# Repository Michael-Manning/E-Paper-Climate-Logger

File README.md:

# Weathergotchi - an E-Paper Climate Logger

## About

This project is an open-source, battery-powered temperature and humidity data logger with an always-on e-paper display. It records ambient conditions over time, stores readings in non-volatile memory, and displays current data along with a history graph. The device is designed for low power consumption, over 2 weeks of operation on a small Li‑Po battery.

Key features:

- ESP32-S3 with deep sleep & RTC timer to wake up
- Temperature and humidity sensor with external EEPROM for logging
- Accurate battery monitoring and charging management
- Power button controller to turn on/off
- 1.54‑inch e‑paper display
- Custom PCB & 3D‑printed case
- Over 2 weeks of battery life on a single charge

The entire project is open source, including hardware schematics, PCB layout, firmware, and enclosure CAD files. A detailed build video is available on YouTube: [E-Paper Climate Logger](https://www.youtube.com/watch?v=I44iGj7gLGA).

### Youtube video

## Repository Structure

```
E-Paper-Climate-Logger/
├── CAD/                 # 3D case design (OpenSCAD source and STL exports)
├── PCB/                 # KiCad hardware design, schematics, datasheets, references
├── firmware/            # PlatformIO firmware (ESP32-S3, Arduino framework)
├── LICENSE              # License file
└── README.md            # This file
```

### CAD

Contains the parametric OpenSCAD models for the front and back case halves, assembly files, and exported STLs for 3D printing. The design is fully parametric – dimensions can be adjusted by editing `constants.scad`.

### PCB

All hardware design files for the custom mainboard (`templog_mainboard`). This directory includes:

- KiCad project files (`.kicad_sch`, `.kicad_pcb`, `.kicad_pro`)
- Schematic sheets for power management and display driver
- Component footprints and 3D models
- Datasheets for all major ICs (charger, fuel gauge, RTC, sensors, etc.)
- Reference schematics from SparkFun and Waveshare

To view or modify the PCB design, install KiCad 9 or later and open `templog_mainboard.kicad_pro`.

### Firmware

PlatformIO project for the ESP32‑S3 using the Arduino framework. It handles sensor reading, timekeeping, data logging to EEPROM, e‑paper display updates, button handling, and power management (deep sleep, wake sources). See `firmware/README.md` for detailed build and flashing instructions.

## Getting Started

### Hardware Prerequisites

- Assembled E-Paper Climate Logger PCB (or a hand‑soldered prototype – note that many components are small and may require reflow soldering)
- 1.54‑inch e‑paper display (compatible with Waveshare pinout)
- 3D‑printed case (files in `CAD/export/`)
- Li‑Po battery (e.g., 400 mAh, single cell)
- USB‑C cable for charging and programming

### Building the Firmware

1. Install [PlatformIO Core](https://platformio.org/install/cli) (or use the PlatformIO extension in VS Code).
2. Navigate to the `firmware` directory.
3. Connect the device via USB‑C.
4. Run:

   ```
   pio run --target upload
   ```

5. Monitor serial output (optional):

   ```
   pio device monitor
   ```

For detailed firmware documentation, including folder structure, driver details, and low‑power operation, refer to [`firmware/README.md`](firmware/README.md).

### Enclosure Assembly

Print the STL files from `CAD/V2/export/` using a high‑resolution FDM printer (0.08 mm layer height recommended). The case uses M2 heat set inserts and M2 screws. Insert the PCB and battery, then screw the front and back halves together. See note.txt in CAD\V2 for more details.

## Hardware Overview

All I2C peripherals (SHT45, DS3231, 24LC512, BQ27441) share the same bus. The e‑paper display is driven via SPI, and the LTC2954 soft power button controls system power-off via the BQ24075.

For complete schematics and PCB layout, open the KiCad project in `PCB/templog_mainboard/`.

## Power Management and Low‑Power Operation

The device is designed to run for over 2 weeks on a small battery:

- In deep sleep, the ESP32‑S3 draws less than 20 µA. The DS3231 and BQ27441 remain active with negligible current.
- The DS3231 alarm wakes the ESP32 at a configurable interval (default: 1 minute). The ESP32 wakes, logs a reading (about 400 ms at 50 mA), updates the display, and returns to sleep.
- The LTC2954 provides a true on/off capability.

## Issues
- **Battery accuracy issues**: In my testing, the reported battery state of charge is not accurate. I believe this is due to a misconfiguration BQ27441.
- **Low battery issues**: In my testing, when connecting a battery to the device, it will sometimes not turn on until the battery has been connected/disconnected multiple times. 

## Notes on building your own device

I don't have a detailed build guide on how to build your own device at this time, but if you do decide to make one, these are some details you should know.

- First firmware upload requires putting the ESP32-S3 in boot mode. There are three pads near the battery input that expose, BOOT, Enable, and ground. Attaching leads to these pins will allow you to put the ESP32 in boot mode.
- The back of the PCB must be completely flat in order to fit in the case with the screen. After soldering through-hole components. like the buttons, you may need a dremel to flatten the leads/solder on the back of the PCB.

## Troubleshooting

- **Device does not power/stay on:** Ensure the battery is charged to at least 3.7V and try disconnecting/reconnecting the battery. Sometimes the battery must be reconnected multiple times before booting for the first time.
- **Battery percentage inaccurate:** The BQ27441 requires a one-time capacity configuration; refer to the datasheet and adjust `BQ27441.cpp`. The fuel gauge also needs to "learn" the battery before it reports an accurate  state of charge. Fully charge the battery, then wait for it to completely deplete. This will help the fuel gauge report a more accurate charge level.
- **Cannot upload program to the device:** Before uploading for the first time, the device must be manually put in boot mode. See the above note in building your own device.

## Limitations
- **Temperature accuracy during handling**: The ESP32 generates heat when active, which can affect the SHT45 reading. The firmware reads the sensor immediately upon wake to minimize this error. Prolonged menu browsing or holding the device will skew the ambient reading for several minutes.
- **Display low‑temperature limit**: The e‑paper module is rated for operation above 0°C. Below freezing, the screen may not update reliably. Data logging continues in the background, and display functionality resumes when the temperature rises.
- **No wireless connectivity**: While this device has the physical capability for bluetooth and WIFI, The current version of the firmware does not support it or allow you to use the radio to export data. Data can be viewed only on the device screen.

## Contributing

Issues, pull requests, and suggestions are welcome. Please follow the existing code style and document any changes to the hardware or firmware.

## License

Refer to the `LICENSE` file in the root directory for licensing terms (open source, permissive).

## Acknowledgements

- SparkFun for the Battery Babysitter reference design
- Waveshare for e‑paper display modules and driver schematics
- The PlatformIO and GxEPD2 communities

For questions or discussions, open an issue on GitHub or visit the YouTube video comments.

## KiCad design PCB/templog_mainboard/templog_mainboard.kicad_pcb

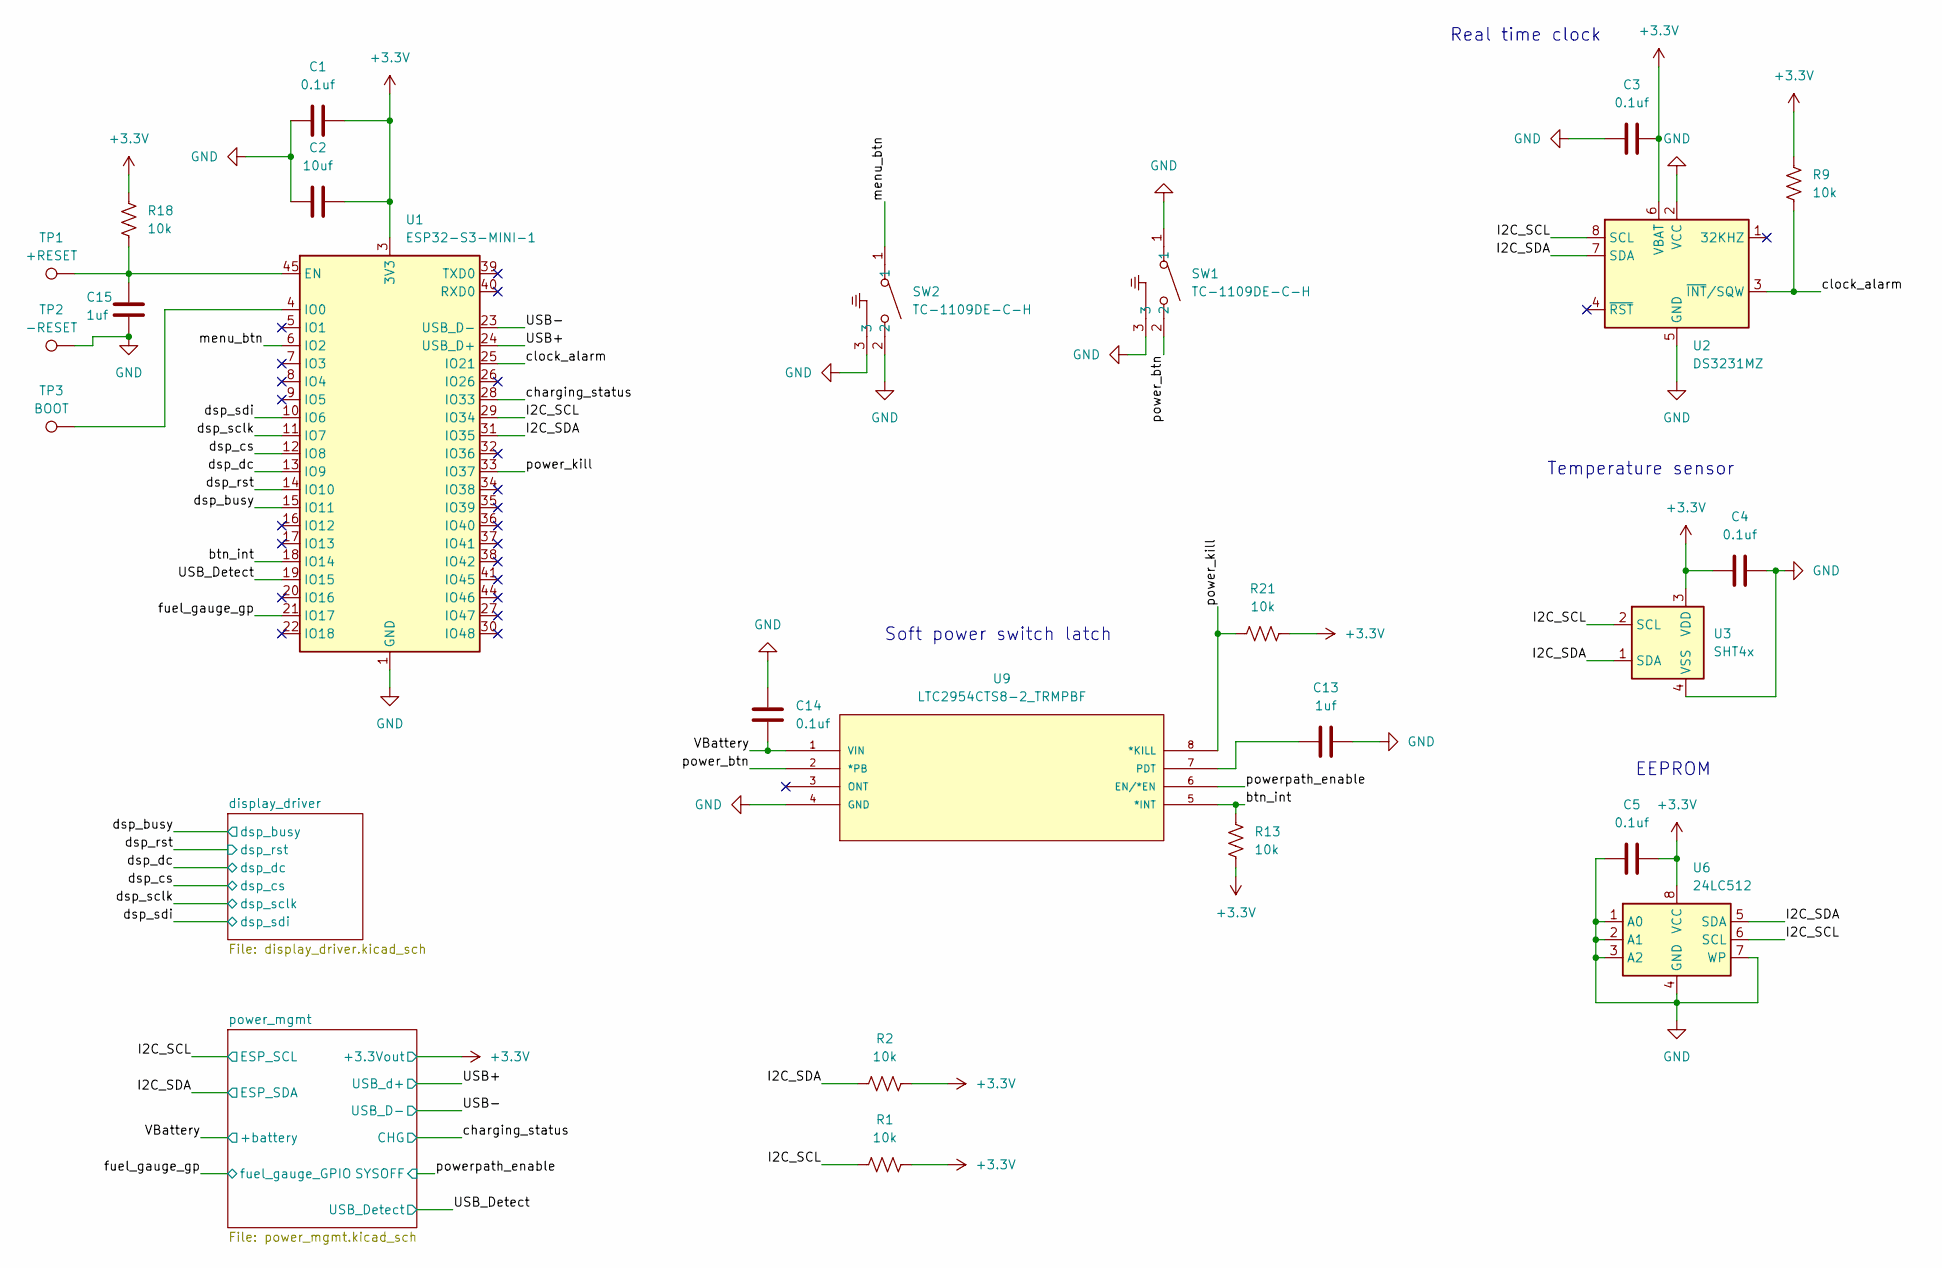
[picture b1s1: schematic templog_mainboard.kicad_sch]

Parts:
C1, C3, C4, C5, C14: 0.1uf; C_0402_1005Metric
C2: 10uf; C_0805_2012Metric
C13: 1uf; C_0603_1608Metric
C15: 1uf; C_0402_1005Metric
R1, R2, R9, R13, R18, R21: 10k; R_0402_1005Metric
SW1, SW2: TC-1109DE-C-H; SW-TH_TC-1109DE-C-H; LCSC Part C400335
TP1: +RESET; TestPoint_Pad_1.0x1.0mm
TP2: -RESET; TestPoint_Pad_1.0x1.0mm
TP3: BOOT; TestPoint_Pad_1.0x1.0mm
U1: ESP32-S3-MINI-1; ESP32-S2-MINI-1; LCSC Part # C2913206
U2: DS3231MZ; SOIC-8_3.9x4.9mm_P1.27mm; LCSC Part # C107410
U3: SHT4x; Sensirion_DFN-4_1.5x1.5mm_P0.8mm_SHT4x_NoCentralPad; LCSC Part # C5360602
U6: 24LC512; SOIC-8_3.9x4.9mm_P1.27mm; LCSC Part # C52088
U9: LTC2954CTS8-2_TRMPBF; TSOT-23_TS8; MANUFACTURER_PART_NUMBER ltc2954cts81; LCSC Part # C580656

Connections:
+3.3V: C1.2, C2.2, C3.2, C4.1, C5.2, R1.2, R2.2, R9.1, R13.2, R18.1, R21.1, U1.3 (3V3), U2.6 (VBAT), U3.3 (VDD), U6.8 (VCC); also elsewhere on the board
/I2C_SCL: R1.1, U1.29 (IO34), U2.8 (SCL), U3.2 (SCL), U6.6 (SCL); also elsewhere on the board
/I2C_SDA: R2.1, U1.31 (IO35), U2.7 (SDA), U3.1 (SDA), U6.5 (SDA); also elsewhere on the board
/USB+: U1.24 (USB_D+); also elsewhere on the board
/USB-: U1.23 (USB_D-); also elsewhere on the board
/USB_Detect: U1.19 (IO15); also elsewhere on the board
/VBattery: C14.1, U9.1 (VIN); also elsewhere on the board
/btn_int: R13.1, U1.18 (IO14), U9.5 (*INT)
/charging_status: U1.28 (IO33); also elsewhere on the board
/clock_alarm: R9.2, U1.25 (IO21), U2.3 (~INT/SQW)
/dsp_busy: U1.15 (IO11); also elsewhere on the board
/dsp_cs: U1.12 (IO8); also elsewhere on the board
/dsp_dc: U1.13 (IO9); also elsewhere on the board
/dsp_rst: U1.14 (IO10); also elsewhere on the board
/dsp_sclk: U1.11 (IO7); also elsewhere on the board
/dsp_sdi: U1.10 (IO6); also elsewhere on the board
/fuel_gauge_gp: U1.21 (IO17); also elsewhere on the board
/menu_btn: SW2.1, U1.6 (IO2)
/power_btn: SW1.2, U9.2 (*PB)
/power_kill: R21.2, U1.33 (IO37), U9.8 (*KILL)
/powerpath_enable: U9.6 (EN/*EN); also elsewhere on the board
GND: C1.1, C2.1, C3.1, C4.2, C5.1, C13.2, C14.2, C15.2, SW1.1, SW1.3, SW2.2, SW2.3, TP2.1, U1.1 (GND), U1.2 (GND), U1.42 (GND), U1.43 (GND), U1.46 (GND), U1.47 (GND), U1.48 (GND), U1.49 (GND), U1.50 (GND), U1.51 (GND), U1.52 (GND), U1.53 (GND), U1.54 (GND), U1.55 (GND), U1.56 (GND), U1.57 (GND), U1.58 (GND), U1.59 (GND), U1.60 (GND), U1.61 (GND), U1.62 (GND), U1.63 (GND), U1.64 (GND), U1.65 (GND), U2.2 (VCC), U2.5 (GND), U3.4 (VSS), U6.1 (A0), U6.2 (A1), U6.3 (A2), U6.4 (GND), U6.7 (WP), U9.4 (GND); also elsewhere on the board
unnamed: C15.1, R18.2, TP1.1, U1.45 (EN)
unnamed: TP3.1, U1.4 (IO0)
unnamed: C13.1, U9.7 (PDT)

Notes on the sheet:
Soft power switch latch
Real time clock
Temperature sensor
EEPROM

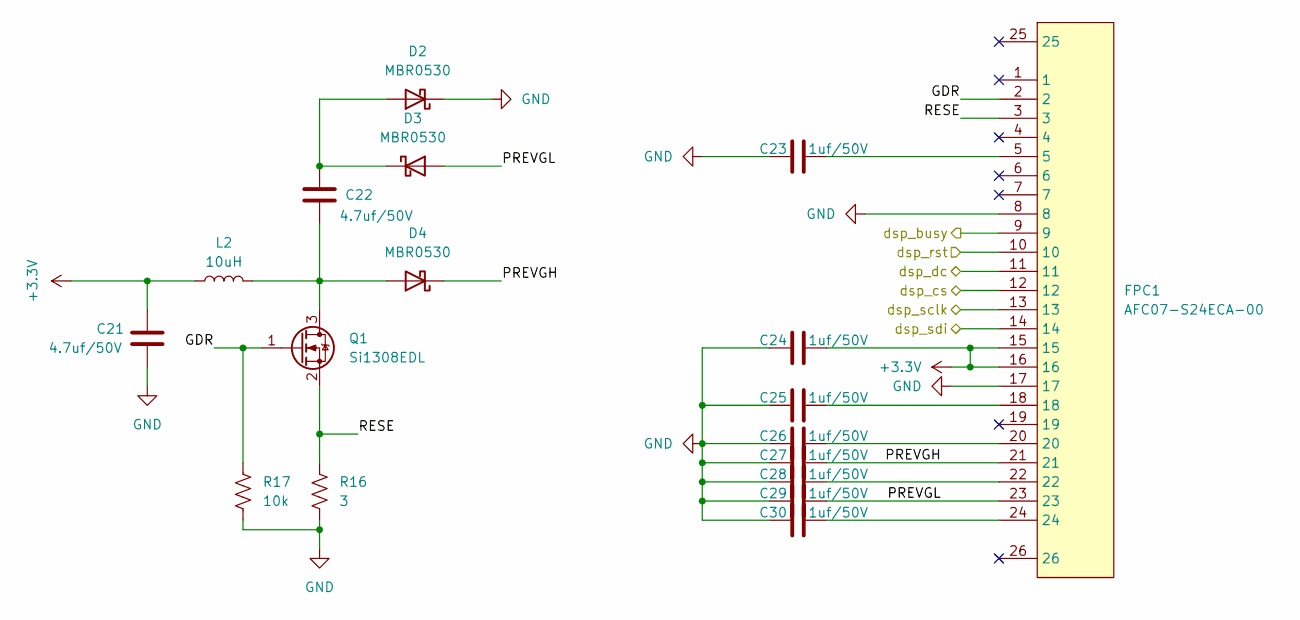
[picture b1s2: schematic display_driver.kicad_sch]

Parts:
C21, C22: 4.7uf/50V; C_0805_2012Metric
C23, C24, C25, C26, C27, C28, C29, C30: 1uf/50V; C_0603_1608Metric
D2, D3: MBR0530; D_SOD-123
D4: MBR0530; D_SOD-123; LCSC Part # C77336
FPC1: AFC07-S24ECA-00; FPC-SMD_AFC07-S24ECA-00; LCSC Part # C262643
L2: 10uH; L_Sunlord_SWPA4030S; LCSC Part # C38117
Q1: Si1308EDL; SOT-323_SC-70; LCSC Part # C469327
R16: 3; R_0402_1005Metric
R17: 10k; R_0402_1005Metric

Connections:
+3.3V: C21.1, C24.2, FPC1.15, FPC1.16, L2.1; also elsewhere on the board
/display_driver/GDR: FPC1.2, Q1.1 (G), R17.2
/display_driver/PREVGH: C27.2, D4.1 (K), FPC1.21
/display_driver/PREVGL: C29.2, D3.2 (A), FPC1.23
/display_driver/RESE: FPC1.3, Q1.2 (S), R16.2
/dsp_busy: FPC1.9; also elsewhere on the board
/dsp_cs: FPC1.12; also elsewhere on the board
/dsp_dc: FPC1.11; also elsewhere on the board
/dsp_rst: FPC1.10; also elsewhere on the board
/dsp_sclk: FPC1.13; also elsewhere on the board
/dsp_sdi: FPC1.14; also elsewhere on the board
GND: C21.2, C23.1, C24.1, C25.1, C26.1, C27.1, C28.1, C29.1, C30.1, D2.1 (K), FPC1.8, FPC1.17, R16.1, R17.1; also elsewhere on the board
unnamed: C23.2, FPC1.5
unnamed: C25.2, FPC1.18
unnamed: C26.2, FPC1.20
unnamed: C28.2, FPC1.22
unnamed: C30.2, FPC1.24
unnamed: C22.1, D2.2 (A), D3.1 (K)
unnamed: C22.2, D4.2 (A), L2.2, Q1.3 (D)

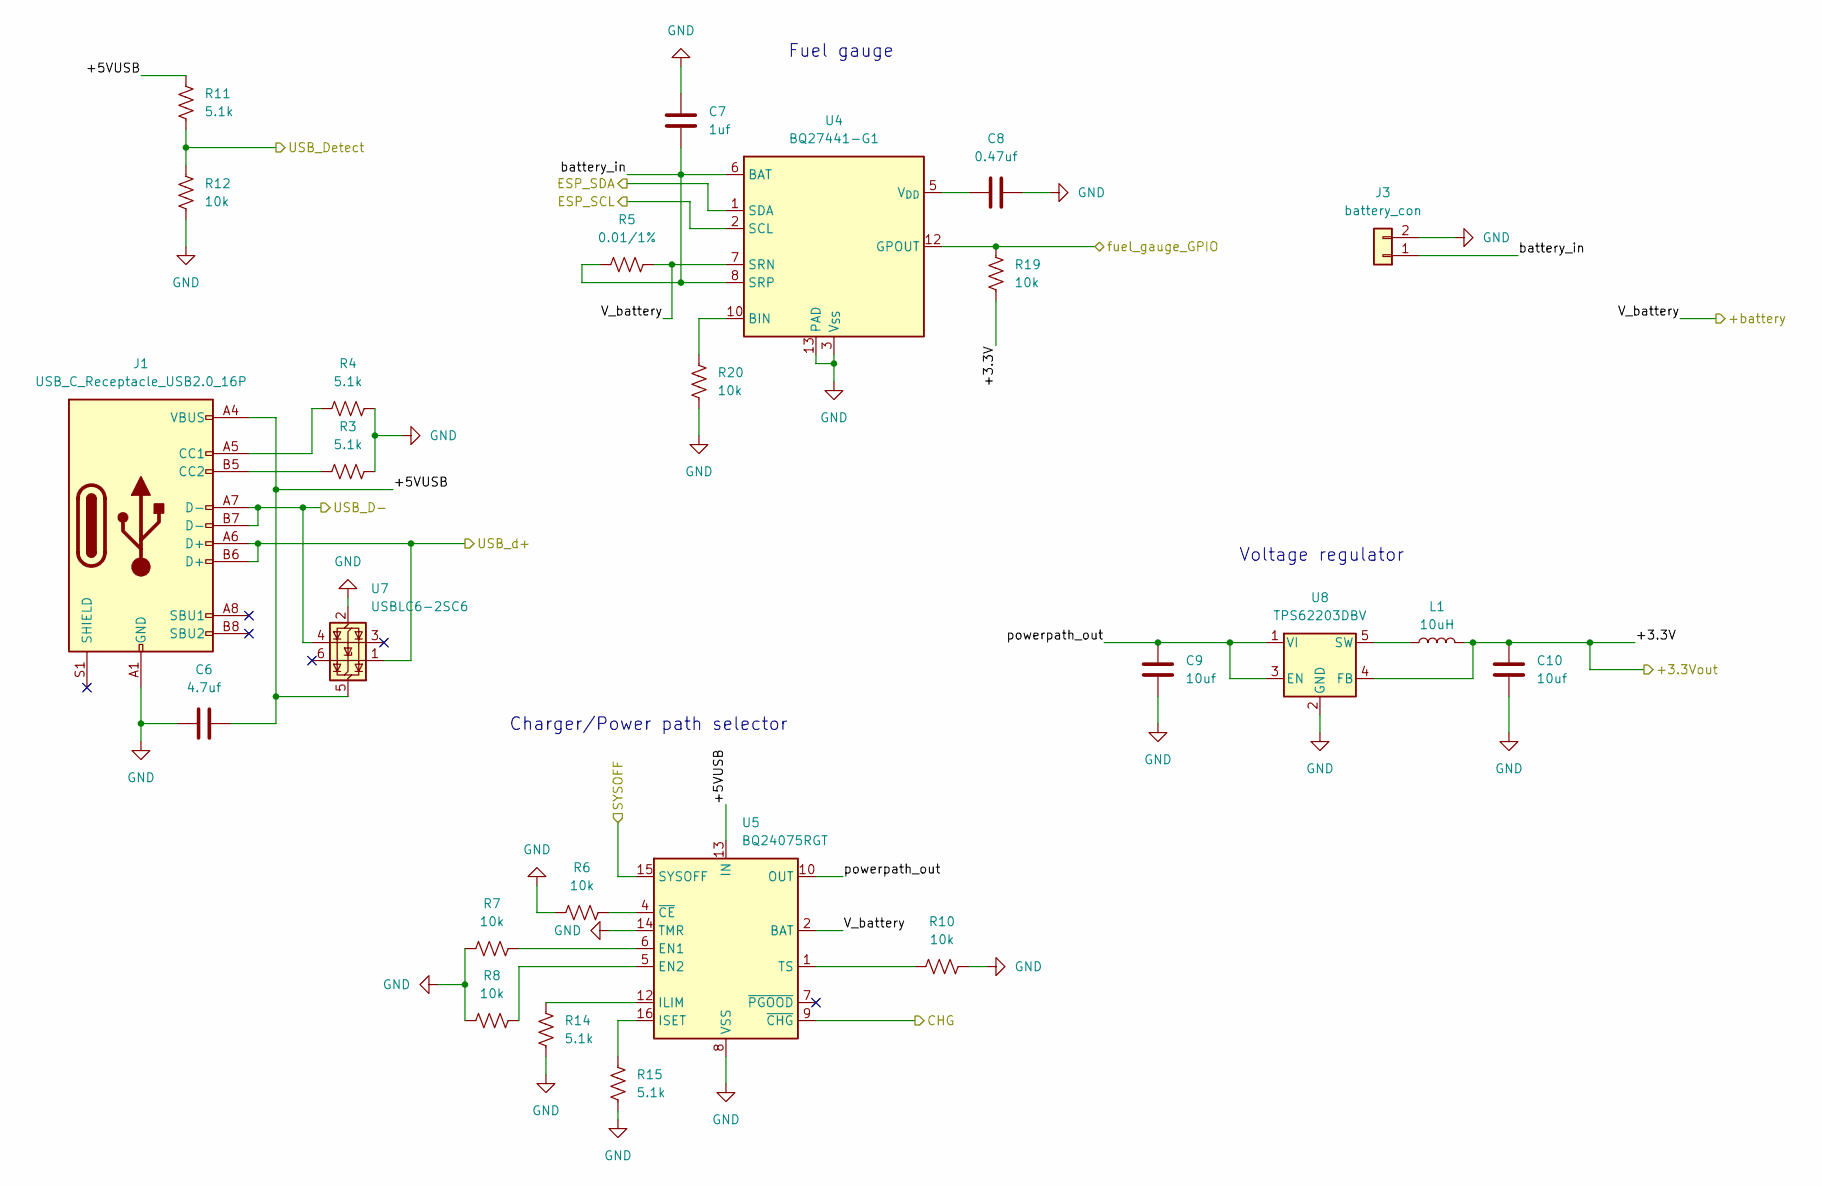
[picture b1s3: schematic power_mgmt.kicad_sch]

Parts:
C6: 4.7uf; C_0603_1608Metric
C7: 1uf; C_0402_1005Metric
C8: 0.47uf; C_0402_1005Metric
C9, C10: 10uf; C_0805_2012Metric
J1: USB_C_Receptacle_USB2.0_16P; USB_C_Receptacle_GCT_USB4105-xx-A_16P_TopMnt_Horizontal
J3: battery_con; JST_PH_S2B-PH-K_1x02_P2.00mm_Horizontal
L1: 10uH; L_Sunlord_SWPA4030S; LCSC Part # C38117
R3, R4, R11, R14, R15: 5.1k; R_0402_1005Metric
R5: 0.01/1%; R_0603_1608Metric
R6, R7, R8, R10, R12, R19, R20: 10k; R_0402_1005Metric
U4: BQ27441-G1; Texas_S-PDSO-N12; LCSC Part # C473374
U5: BQ24075RGT; VQFN-16-1EP_3x3mm_P0.5mm_EP1.6x1.6mm; LCSC Part # C15464
U7: USBLC6-2SC6; SOT-23-6; LCSC Part # C7519
U8: TPS62203DBV; SOT-23-5; LCSC Part # C9051

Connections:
+3.3V: C10.2, L1.2, R19.1, U8.4 (FB); also elsewhere on the board
/I2C_SCL: U4.2 (SCL); also elsewhere on the board
/I2C_SDA: U4.1 (SDA); also elsewhere on the board
/USB+: J1.A6 (D+), J1.B6 (D+), U7.1 (I/O1); also elsewhere on the board
/USB-: J1.A7 (D-), J1.B7 (D-), U7.4 (I/O2); also elsewhere on the board
/USB_Detect: R11.1, R12.2; also elsewhere on the board
/VBattery: R5.2, U4.7 (SRN), U5.2 (BAT), U5.3 (BAT); also elsewhere on the board
/charging_status: U5.9 (~CHG); also elsewhere on the board
/fuel_gauge_gp: R19.2, U4.12 (GPOUT); also elsewhere on the board
/power_mgmt/+5VUSB: C6.1, J1.A4 (VBUS), J1.A9 (VBUS), J1.B4 (VBUS), J1.B9 (VBUS), R11.2, U5.13 (IN), U7.5 (VBUS)
/power_mgmt/battery_in: C7.2, J3.1, R5.1, U4.6 (BAT), U4.8 (SRP)
/power_mgmt/powerpath_out: C9.2, U5.10 (OUT), U5.11 (OUT), U8.1 (VI), U8.3 (EN)
/powerpath_enable: U5.15 (SYSOFF); also elsewhere on the board
GND: C6.2, C7.1, C8.1, C9.1, C10.1, J1.A1 (GND), J1.A12 (GND), J1.B1 (GND), J1.B12 (GND), J3.2, R3.2, R4.2, R6.1, R7.1, R8.1, R10.2, R12.1, R14.1, R15.1, R20.2, U4.3 (V_{SS}), U4.13 (PAD), U5.8 (VSS), U5.14 (TMR), U5.17 (VSS), U7.2 (GND), U8.2 (GND); also elsewhere on the board
unnamed: J1.A5 (CC1), R4.1
unnamed: J1.B5 (CC2), R3.1
unnamed: R20.1, U4.10 (BIN)
unnamed: C8.2, U4.5 (V_{DD})
unnamed: R7.2, U5.6 (EN1)
unnamed: R8.2, U5.5 (EN2)
unnamed: R14.2, U5.12 (ILIM)
unnamed: R15.2, U5.16 (ISET)
unnamed: R10.1, U5.1 (TS)
unnamed: R6.2, U5.4 (~CE)
unnamed: L1.1, U8.5 (SW)

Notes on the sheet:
Voltage regulator
Charger/Power path selector
Fuel gauge

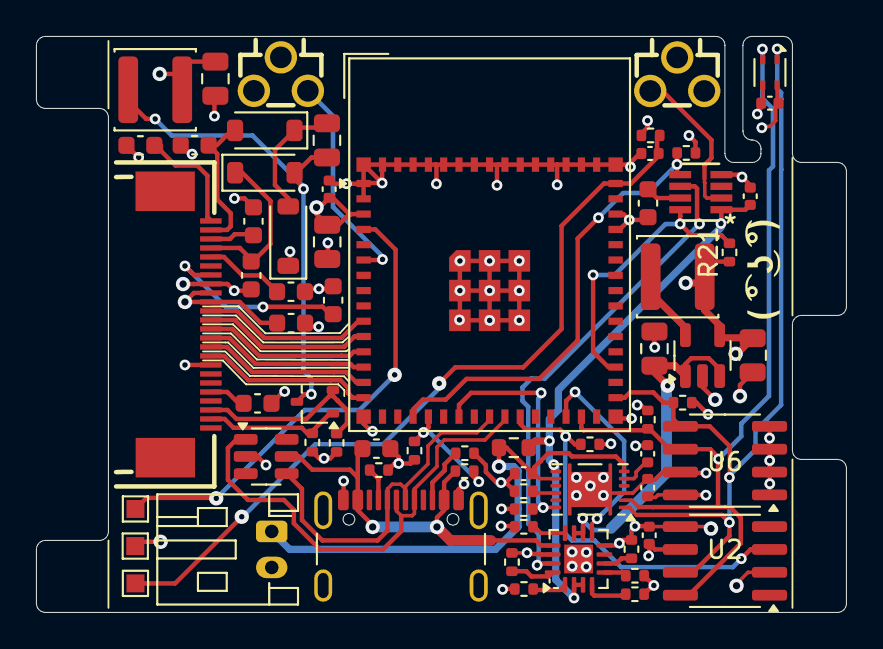
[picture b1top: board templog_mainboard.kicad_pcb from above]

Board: 4 copper layers, 45.0 x 32.0 mm, 67 parts (0 on the bottom side), 50 nets.

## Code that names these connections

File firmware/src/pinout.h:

#pragma once

namespace pins{
   constexpr int menuBtn = 2;
   constexpr int dsp_SDI = 6;
   constexpr int dsp_CLK = 7;
   constexpr int dsp_CS = 8;
   constexpr int dsp_DC = 9;
   constexpr int dsp_RST = 10;
   constexpr int dsp_BUSY = 11;
   constexpr int powerBtn = 14; 
   constexpr int USBDetect = 15; 
   constexpr int fuelGaugeGPIO = 17;
   constexpr int clockAlarm = 21; 
   constexpr int chargeStatus = 33;   
   constexpr int SCL = 34;   
   constexpr int SDA = 35;   
   constexpr int powerKill = 37;   
}

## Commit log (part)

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2026-05-31 initial public commit
2026-05-31 images
2026-05-31 Add README
2026-05-31 Add MIT License
2026-06-03 update PCB notes
2026-06-04 remove cryptic comments about fuelGuageGPIO
2026-06-05 fix: removed implicit conversion by stting to int instead
2026-06-05 added readme
2026-06-05 added to readme fw
2026-06-05 added main readme
2026-06-05 updated youtube thumbnail
2026-06-05 changing folder name
2026-06-06 add to readme
2026-06-06 updated timing of readme
2026-06-08 readme accuracy and removed default upload port
2026-06-08 removed inaccurate hardware diagram
2026-06-08 practical troubleshooting
2026-06-08 added known issues
2026-06-08 remove schematic
